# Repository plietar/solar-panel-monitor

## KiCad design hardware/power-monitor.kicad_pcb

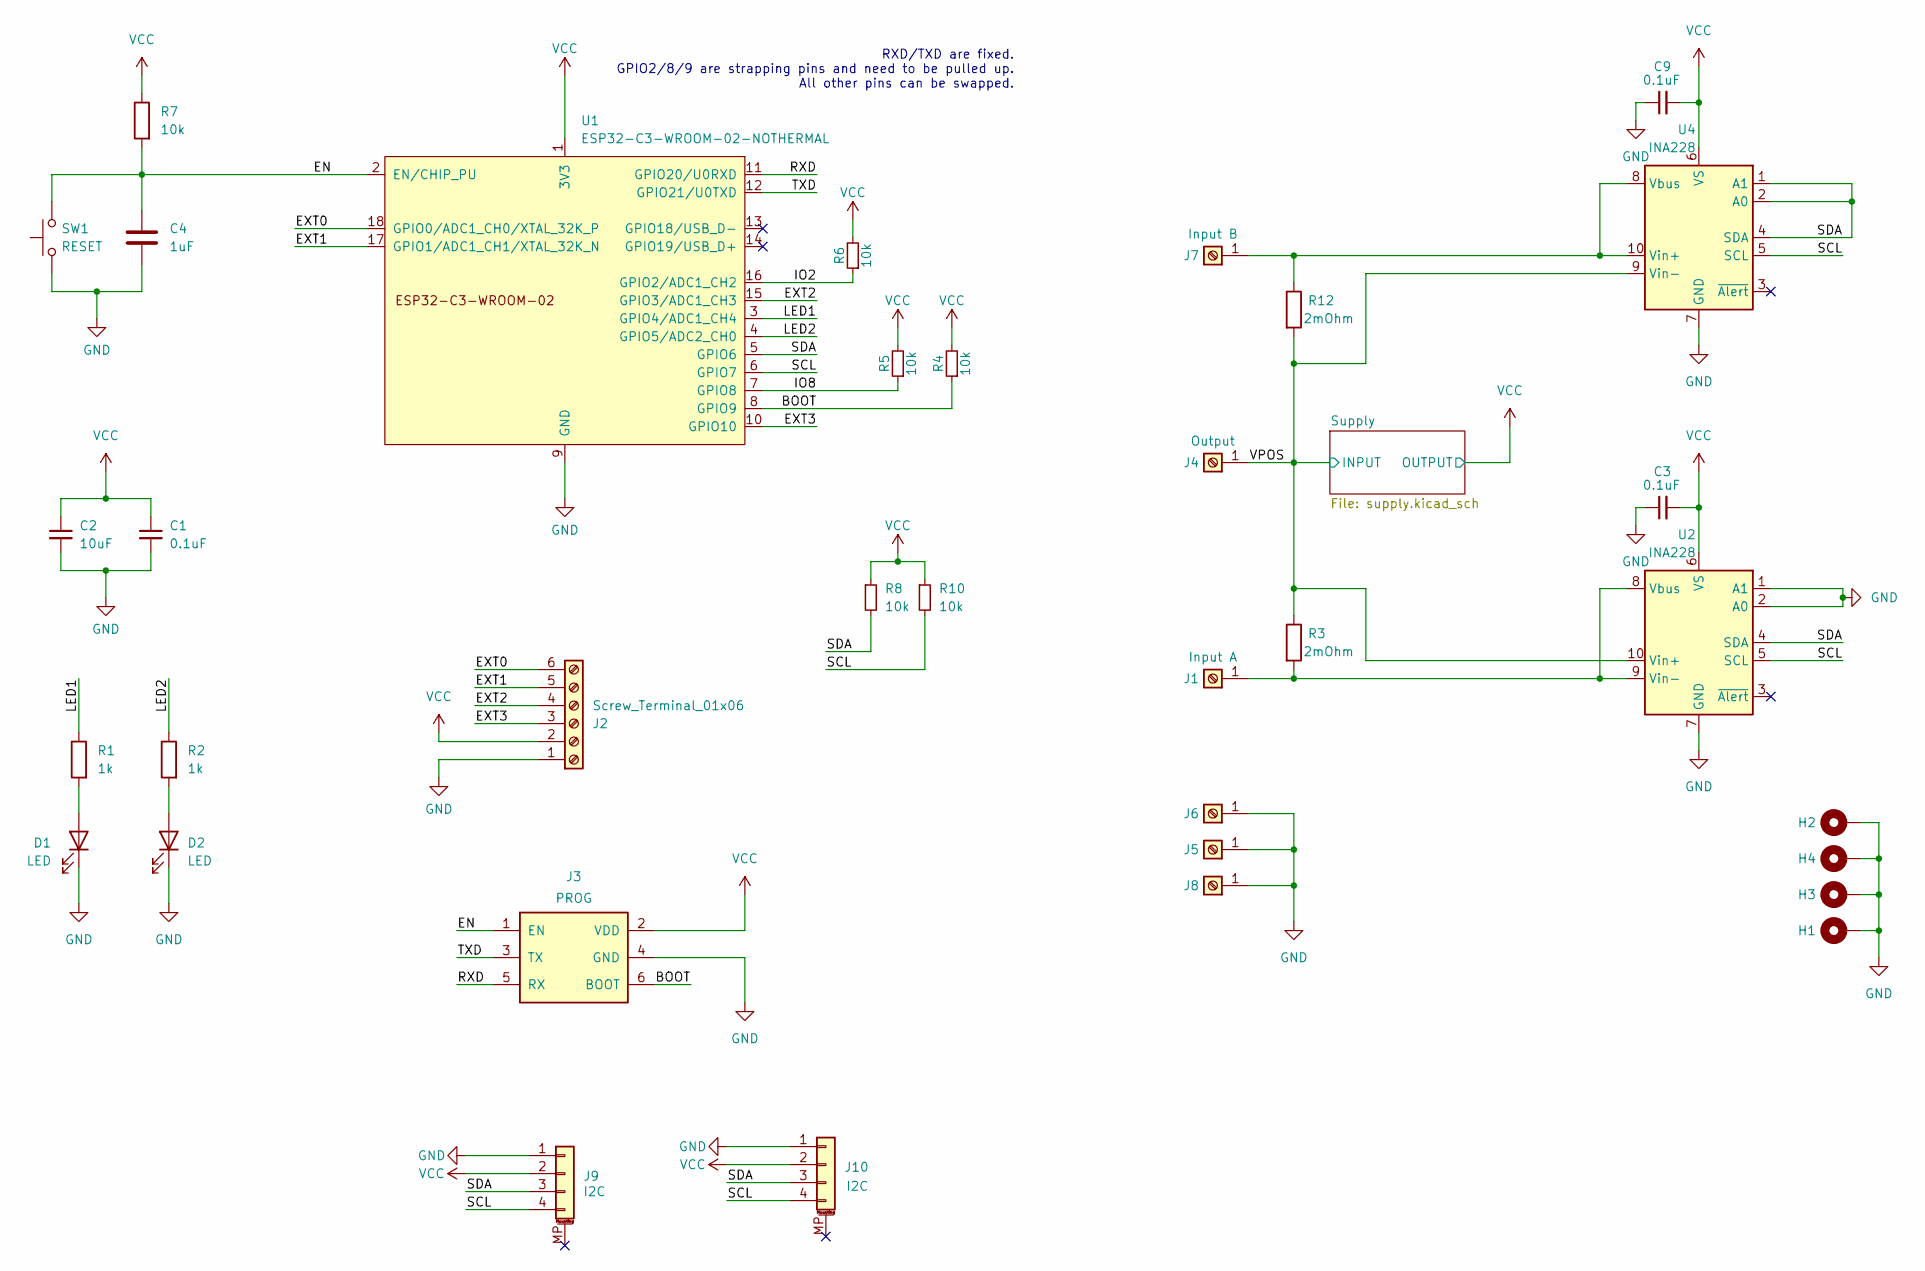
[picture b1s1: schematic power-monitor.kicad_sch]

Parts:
C1: 0.1uF; C_1206_3216Metric_Pad1.33x1.80mm_HandSolder
C2: 10uF; C_1206_3216Metric_Pad1.33x1.80mm_HandSolder
C3, C9: 0.1uF; C_0603_1608Metric_Pad1.08x0.95mm_HandSolder
C4: 1uF; C_1206_3216Metric_Pad1.33x1.80mm_HandSolder
D1, D2: LED; LED_1206_3216Metric_Pad1.42x1.75mm_HandSolder
H1, H2, H3, H4: MountingHole_Pad; MountingHole_2.2mm_M2_Pad
J1, J4, J5, J6, J7, J8: Wuerth_REDCUBE-THR_WP-THRSH_74651175_THR
J2: Screw_Terminal_01x06; TerminalBlock_Phoenix_MPT-0,5-6-2.54_1x06_P2.54mm_Horizontal
J3: Tag-Connect_TC2030-IDC-NL_2x03_P1.27mm_Vertical
J9: JST_PH_S4B-PH-SM4-TB_1x04-1MP_P2.00mm_Horizontal
J10: JST_SH_SM04B-SRSS-TB_1x04-1MP_P1.00mm_Horizontal
R1, R2: 1k; R_1206_3216Metric_Pad1.30x1.75mm_HandSolder
R3, R12: 2mOhm; R_2816_7142Metric_Pad3.20x4.45mm_HandSolder
R4, R5, R6, R7, R8, R10: 10k; R_1206_3216Metric_Pad1.30x1.75mm_HandSolder
SW1: RESET; SW_Push_1P1T_NO_6x6mm_H9.5mm
U1: ESP32-C3-WROOM-02-NOTHERMAL
U2, U4: INA228; VSSOP-10_3x3mm_P0.5mm

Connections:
/BOOT: J3.6 (BOOT), R4.1, U1.8 (GPIO9)
/EN: C4.1, J3.1 (EN), R7.2, SW1.1, U1.2 (EN/CHIP_PU)
/EXT0: J2.6, U1.18 (GPIO0/ADC1_CH0/XTAL_32K_P)
/EXT1: J2.5, U1.17 (GPIO1/ADC1_CH1/XTAL_32K_N)
/EXT2: J2.4, U1.15 (GPIO3/ADC1_CH3)
/EXT3: J2.3, U1.10 (GPIO10)
/IO2: R6.1, U1.16 (GPIO2/ADC1_CH2)
/IO8: R5.1, U1.7 (GPIO8)
/LED1: R1.1, U1.3 (GPIO4/ADC1_CH4)
/LED2: R2.1, U1.4 (GPIO5/ADC2_CH0)
/RXD: J3.5 (RX), U1.11 (GPIO20/U0RXD)
/SCL: J9.4, J10.4, R10.2, U1.6 (GPIO7), U2.5 (SCL), U4.5 (SCL)
/SDA: J9.3, J10.3, R8.2, U1.5 (GPIO6), U2.4 (SDA), U4.1 (A1), U4.2 (A0), U4.4 (SDA)
/TXD: J3.3 (TX), U1.12 (GPIO21/U0TXD)
/VPOS: J4.1, R3.1, R12.2, U2.10 (Vin+), U4.9 (Vin-); also elsewhere on the board
GND: C1.2, C2.2, C3.1, C4.2, C9.1, D1.1 (K), D2.1 (K), H1.1, H2.1, H3.1, H4.1, J2.1, J3.4 (GND), J5.1, J6.1, J8.1, J9.1, J10.1, SW1.2, U1.9 (GND), U2.1 (A1), U2.2 (A0), U2.7 (GND), U4.7 (GND); also elsewhere on the board
unnamed: D1.2 (A), R1.2
unnamed: D2.2 (A), R2.2
unnamed: J1.1, R3.2, U2.8 (Vbus), U2.9 (Vin-)
unnamed: J7.1, R12.1, U4.8 (Vbus), U4.10 (Vin+)
VCC: C1.1, C2.1, C3.2, C9.2, J2.2, J3.2 (VDD), J9.2, J10.2, R4.2, R5.2, R6.2, R7.1, R8.1, R10.1, U1.1 (3V3), U2.6 (VS), U4.6 (VS); also elsewhere on the board

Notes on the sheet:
RXD/TXD are fixed. GPIO2/8/9 are strapping pins and need to be pulled up. All other pins can be swapped.

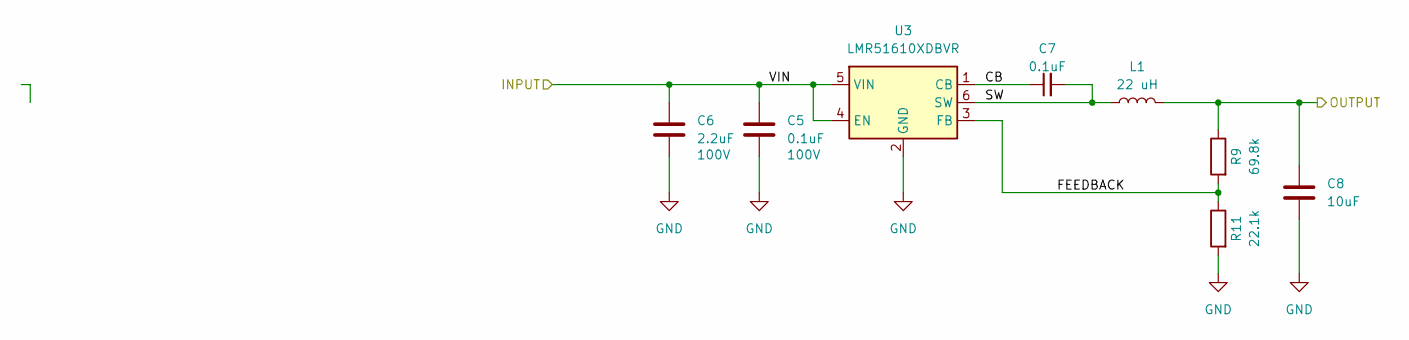
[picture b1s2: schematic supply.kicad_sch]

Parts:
C5, C7: 0.1uF; C_0603_1608Metric_Pad1.08x0.95mm_HandSolder
C6: 2.2uF; C_1206_3216Metric_Pad1.33x1.80mm_HandSolder
C8: 10uF; C_1206_3216Metric_Pad1.33x1.80mm_HandSolder
L1: 22 uH; L_Bourns_SRN6045TA
R9: 69.8k; R_1206_3216Metric_Pad1.30x1.75mm_HandSolder
R11: 22.1k; R_1206_3216Metric_Pad1.30x1.75mm_HandSolder
U3: LMR51610XDBVR; SOT-23-6

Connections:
/Supply/CB: C7.1, U3.1 (CB)
/Supply/FEEDBACK: R9.2, R11.1, U3.3 (FB)
/Supply/SW: C7.2, L1.1, U3.6 (SW)
/VPOS: C5.1, C6.1, U3.4 (EN), U3.5 (VIN); also elsewhere on the board
GND: C5.2, C6.2, C8.2, R11.2, U3.2 (GND); also elsewhere on the board
VCC: C8.1, L1.2, R9.1; also elsewhere on the board

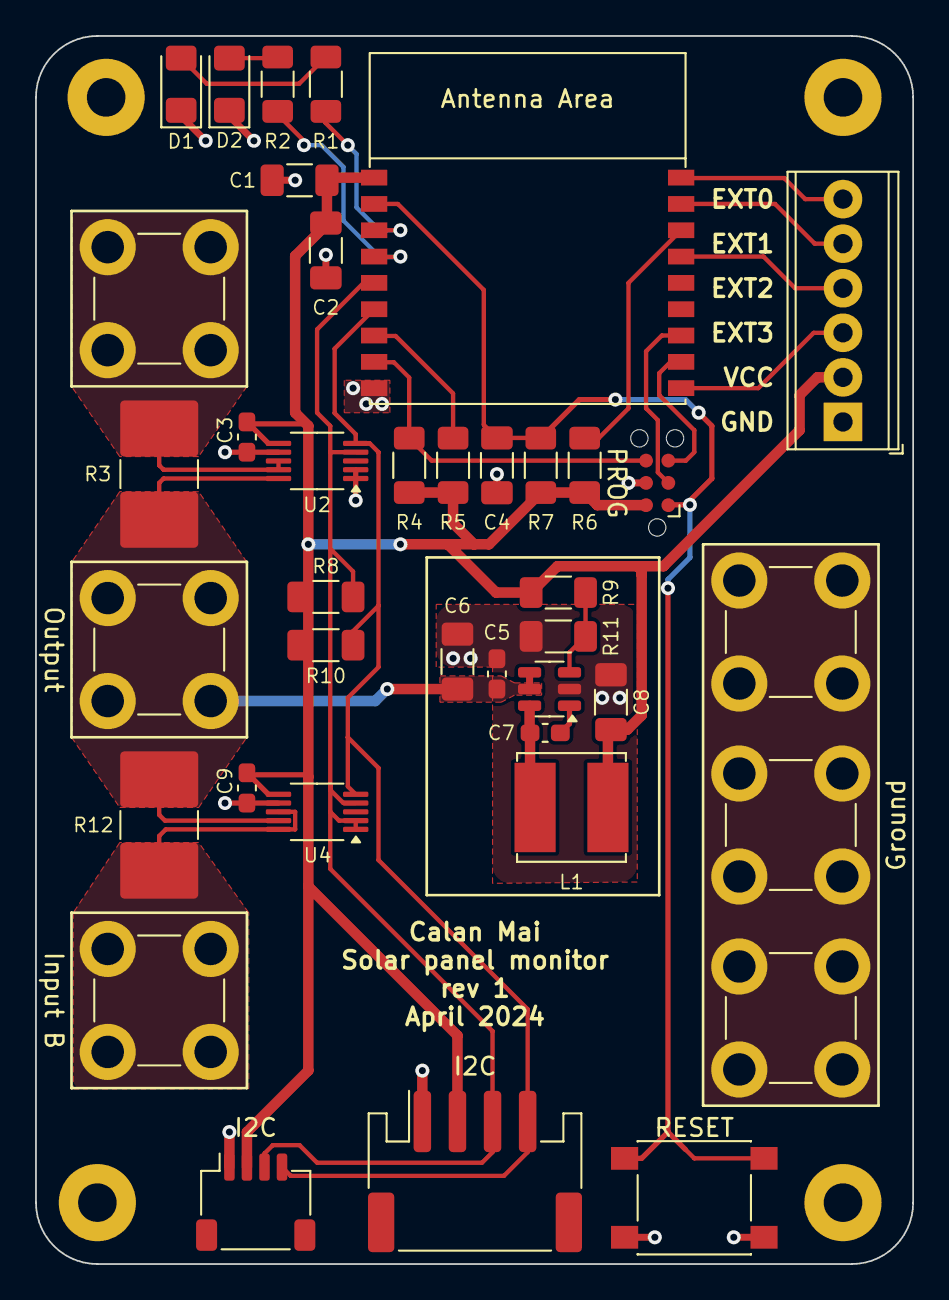
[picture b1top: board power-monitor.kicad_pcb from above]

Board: 2 copper layers, 50.0 x 70.0 mm, 43 parts (0 on the bottom side), 24 nets.

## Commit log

2024-01-26 Initial notes.
2024-01-28 Start working on hardware
2024-02-02 PLC based hardware design
2024-04-02 Remove PLC, use ESP
2024-04-11 rev 1
2024-04-21 Improve BOM
2024-04-21 Autoplace schematic labels.
2024-04-21 Add initial firmware revision.
2024-04-21 Add Github workflow
2024-04-21 Publish interactive BOM to GitHub Pages.
2024-10-11 Freshen up CI
2024-10-11 Remove old file
2024-10-11 Fix build
